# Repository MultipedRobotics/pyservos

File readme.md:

# pyServos

**Still under development**
**Starting to add XL-430 servo**

- pyservos
    - **ServoSerial** - half duplex hardware serial interface using DTR from a USB serial port
    - **PiServoSerial** - half duplex hardware serial interface using a HW pin
    - **utils** - misc
    - **XL320** - register/command/error definitions for Dynamixel's XL-320 servo
    - **AX12** - register/command/error definitions for Dynamixel's AX-12A servo
    - **XL430** - register/command/error definitions for Dynamixel's AX-12A servo

# Setup

## Install

The suggested way to install this is via the `pip` command as follows::

    pip install pyservos

## Development

I am currently using [poetry](https://python-poetry.org/) for my library and using
`pyproject.toml`. To submit git pulls, clone the repository and set it up as
follows:

    git clone https://github.com/MultipedRobotics/pyservos
    cd pyservos
    poetry install
    poety run pytest

# Usage

The `\bin` directory has a number of useful programs to set servo position or ID number. Just
run the command with the `--help` flag to see how to use it.

- `servoAX12`
- `servoXL320` (not implemented)
- `servoXL430` (not implemented)

The above commands have the following format:

 - servoXXX
    - **ping**: find servos on bus, ID[int|**None**]
    - **reboot**: reboot a servo, ID[int|**None**]
    - **reset**: reset a servo, ID[int], level[int]
    - **angle**: set new angle in degrees or radians, angle[float], radians[True|**False**]
    - **baudrate**: set new baudrate, rate[int]
    - **id**: set new ID, current_id[int], new_id[int]
- Values
    - ID: 1-254
    - reset level: 1 (all), 2(all but ID), 3 (all but ID and baudrate)
    - angle: 0-300 degrees
    - rate: 1000000 is default
    - None: if you leave out the value, there is a default that occurs which is safe

# Documentation

- [AX-12A Servo](https://github.com/MomsFriendlyRobotCompany/pyservos/tree/master/docs/ax12)
- [XL-320 Servo](https://github.com/MomsFriendlyRobotCompany/pyservos/tree/master/docs/xl320)
- [XL-430 Servo](https://github.com/MomsFriendlyRobotCompany/pyservos/tree/master/docs/xl430)

A simple example to turn the servo and turn the LED on using a USB serial converter:

```python
# Run an AX-12 servo
from pyservos.servo_serial import ServoSerial
from pyservos.ax12 import AX12

serial = ServoSerial('/dev/tty.usbserial')  # tell it what port you want to use
# serial = ServoSerial('dummy')  # use a dummy serial interface for testing
serial.open()

ax = AX12()
pkt = ax.makeServoPacket(1, 158.6)  # move servo 1 to 158.6 degrees
ret = serial.sendPkt(pkt)  # send packet, I don't do anything with the returned status packet

pkt = ax.makeLEDPacket(1, AX12.LED_ON)
ret = serial.sendPkt(pkt)
```

Although I have made some packet creators (like LED and Servo), you can make
your own using the basic `makeWritePacket` and `makeReadPacket`.

```python
# Run an XL-320 servo
from pyservos.xl320 import XL320
from pyservos.utils import angle2int

xl = XL320()

# let's make our own servo packet that sends servo 3 to 220.1 degrees
ID = 3
reg = XL320.GOAL_POSITION
params = angle2int(220.1)  # convert 220.1 degrees to an int between 0-1023
pkt = xl.makeWritePacket(ID, reg, params)
```

## Dynaixel Servos

## Robot Examples

Here are some example [robots](https://github.com/MultipedRobotics/pyservos/tree/master/docs/robots)

# Other Software

I haven't used these, but they seem good:

- c++: [libdynamixel](https://github.com/resibots/libdynamixel)

# Change Log

| | | |
|------------|-------|--------------------------------------------|
| 2020-01-25 | 2.0.0 | re-architected around protocols rather than servos types |
| 2018-04-30 | 1.0.1 |  API fixes and starting to add 430 support |
| 2018-02-17 | 1.0.0 |  added AX-12 support and renamed the library |
| 2017-04-01 | 0.9.0 |  added python3 support |
| 2017-03-26 | 0.8.0 |  major overhaul and removed the GPIO stuff |
| 2017-03-19 | 0.7.7 |  can switch between GPIO pin and pyserial.setRTS() |
| 2017-02-20 | 0.7.6 |  small fixes and added servo_reboot |
| 2017-01-16 | 0.7.5 |  fixes some small errors |
| 2016-11-29 | 0.7.4 |  add bulk write and small changes |
| 2016-10-11 | 0.7.1 |  small changes/updates |
| 2016-09-12 | 0.7.0 |  refactoring, still working on API |
| 2016-09-05 | 0.5.0 |  published to PyPi |
| 2016-08-16 | 0.0.1 |  init |

# The MIT License (MIT)

Copyright (c) 2016 Kevin J. Walchko

Permission is hereby granted, free of charge, to any person obtaining a copy of
this software and associated documentation files (the "Software"), to deal in
the Software without restriction, including without limitation the rights to
use, copy, modify, merge, publish, distribute, sublicense, and/or sell copies
of the Software, and to permit persons to whom the Software is furnished to do
so, subject to the following conditions:

The above copyright notice and this permission notice shall be included in all
copies or substantial portions of the Software.

THE SOFTWARE IS PROVIDED "AS IS", WITHOUT WARRANTY OF ANY KIND, EXPRESS OR
IMPLIED, INCLUDING BUT NOT LIMITED TO THE WARRANTIES OF MERCHANTABILITY, FITNESS
FOR A PARTICULAR PURPOSE AND NONINFRINGEMENT. IN NO EVENT SHALL THE AUTHORS OR
COPYRIGHT HOLDERS BE LIABLE FOR ANY CLAIM, DAMAGES OR OTHER LIABILITY, WHETHER
IN AN ACTION OF CONTRACT, TORT OR OTHERWISE, ARISING FROM, OUT OF OR IN
CONNECTION WITH THE SOFTWARE OR THE USE OR OTHER DEALINGS IN THE SOFTWARE.

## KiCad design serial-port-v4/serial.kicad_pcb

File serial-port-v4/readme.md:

# Serial Port

## Robotis Suggestion

There are many ways (chip combinations) to achieve this interface.

## My Board

The serial interface talks to both AX-12 (12V power) and XL-320 (8V power)
servos. The design uses SMD parts, but they are all hand solderable.

- RPi TX is attached to a 74LV126 single gate, OE operates when **HIGH**
- RPi RX is attached to a 74LV125 single gate, OE operates when **LOW**
- RPi DTR (any pin really) is connected to the OE on both chips
- Gates are both 5V tolerant on input and have a VCC range of 1.65 - 5.5V
- Both gates are setup for 3.3V operations, with a MOSFET setup to level shift
the DATA line
- The behavior follows the above Robotis suggestion for half duplex operation

[schematic](serial.pdf)

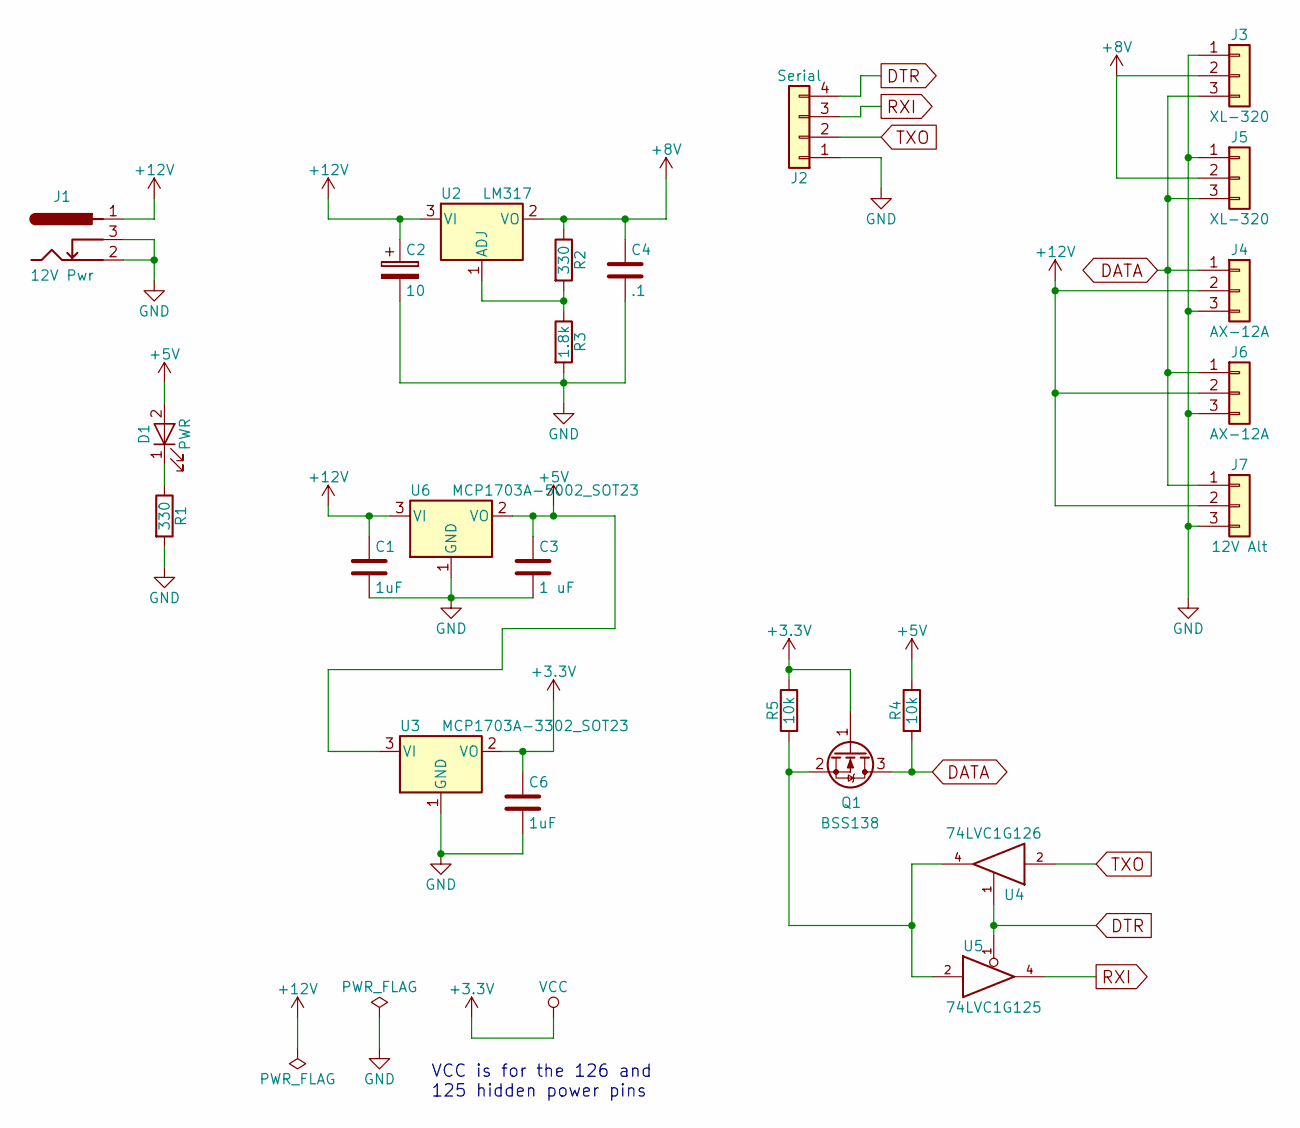
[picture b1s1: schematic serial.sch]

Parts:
C1, C6: 1uF; C_1206_HandSoldering
C2: 10; CP_Radial_D6.3mm_P2.50mm
C3: 1 uF; C_1206_HandSoldering
C4: .1; C_1206_HandSoldering
D1: PWR; LED_1206_HandSoldering
J1: 12V Pwr; BARREL_JACK
J2: Serial; Pin_Header_Straight_1x04_Pitch2.54mm
J3, J5: XL-320; Molex_MicroLatch-53253-0370_03x2.00mm_Straight
J4, J6: AX-12A; Molex_SPOX-5267_22-03-5035_03x2.54mm_Straight
J7: 12V Alt; Pin_Header_Straight_1x03_Pitch2.54mm
Q1: BSS138; SOT-23_Handsoldering
R1, R2: 330; R_1206_HandSoldering
R3: 1.8k; R_1206_HandSoldering
R4, R5: 10k; R_1206_HandSoldering
U2: LM317; TO-220-3_Horizontal
U3: MCP1703A-3302_SOT23; SOT-23_Handsoldering
U4: 74LVC1G126; SOT-23-5_HandSoldering
U5: 74LVC1G125; SOT-23-5_HandSoldering
U6: MCP1703A-5002_SOT23; SOT-23_Handsoldering

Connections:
+3V3: C6.1, Q1.1 (G), R5.1, U3.2 (VO), U4.5 (VCC), U5.5 (VCC)
+5V: C3.1, D1.2 (A), R4.1, U3.3 (VI), U6.2 (VO)
+8V: C4.1, J3.2, J5.2, R2.1, U2.2 (VO)
+12V: C1.1, C2.1, J1.1, J4.2, J6.2, J7.2, U2.3 (VI), U6.3 (VI)
DATA: J3.3, J4.1, J5.3, J6.1, J7.1, Q1.3 (D), R4.2
DTR: J2.4, U4.1, U5.1
GND: C1.2, C2.2, C3.2, C4.2, C6.2, J1.2, J1.3, J2.1, J3.1, J4.3, J5.1, J6.3, J7.3, R1.2, R3.2, U3.1 (GND), U4.3 (GND), U5.3 (GND), U6.1 (GND)
unnamed: D1.1 (K), R1.1
unnamed: Q1.2 (S), R5.2, U4.4, U5.2
unnamed: R2.2, R3.1, U2.1 (ADJ)
RXI: J2.3, U5.4
TXO: J2.2, U4.2

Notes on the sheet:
VCC is for the 126 and 125 hidden power pins

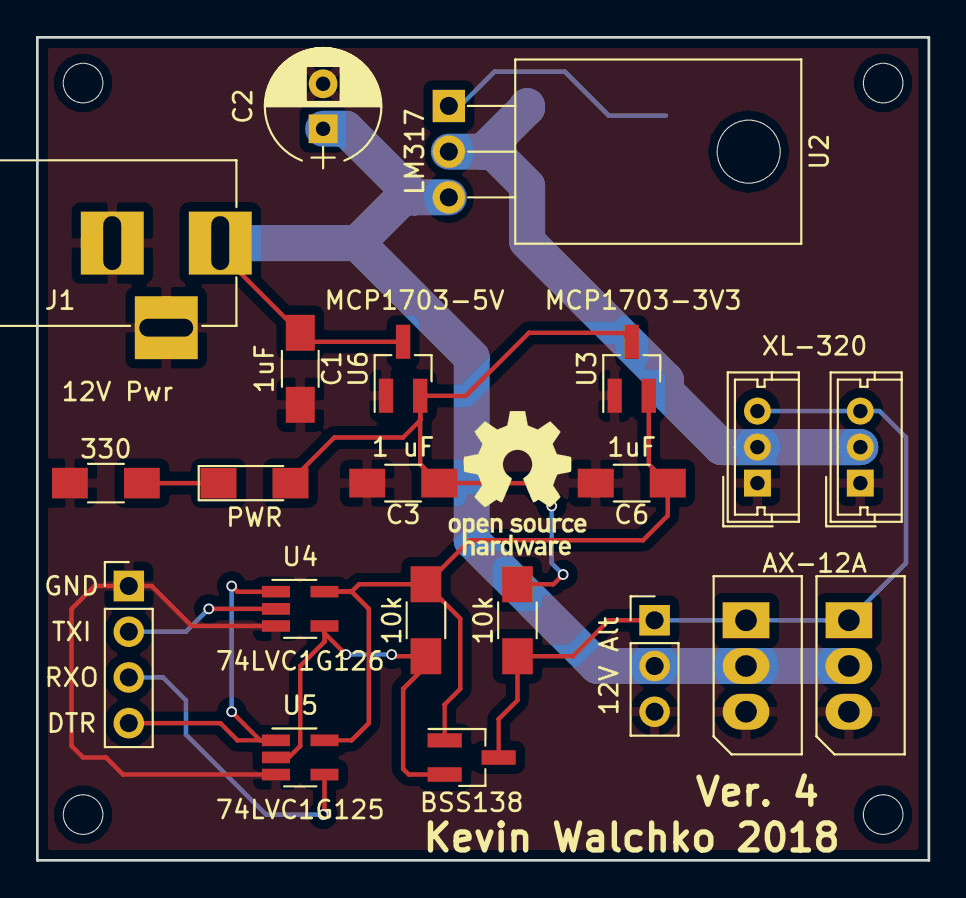
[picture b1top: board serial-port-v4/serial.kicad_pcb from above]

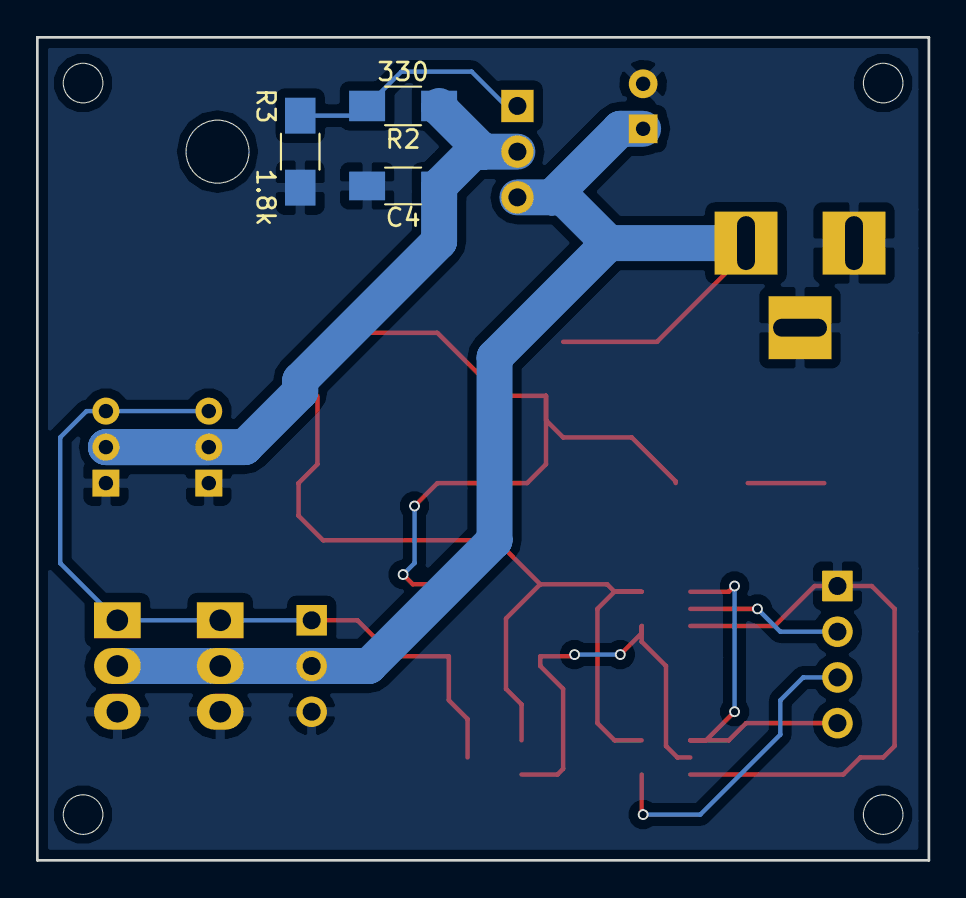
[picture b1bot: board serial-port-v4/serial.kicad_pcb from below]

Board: 2 copper layers, 49.5 x 45.7 mm, 24 parts (3 on the bottom side), 12 nets.

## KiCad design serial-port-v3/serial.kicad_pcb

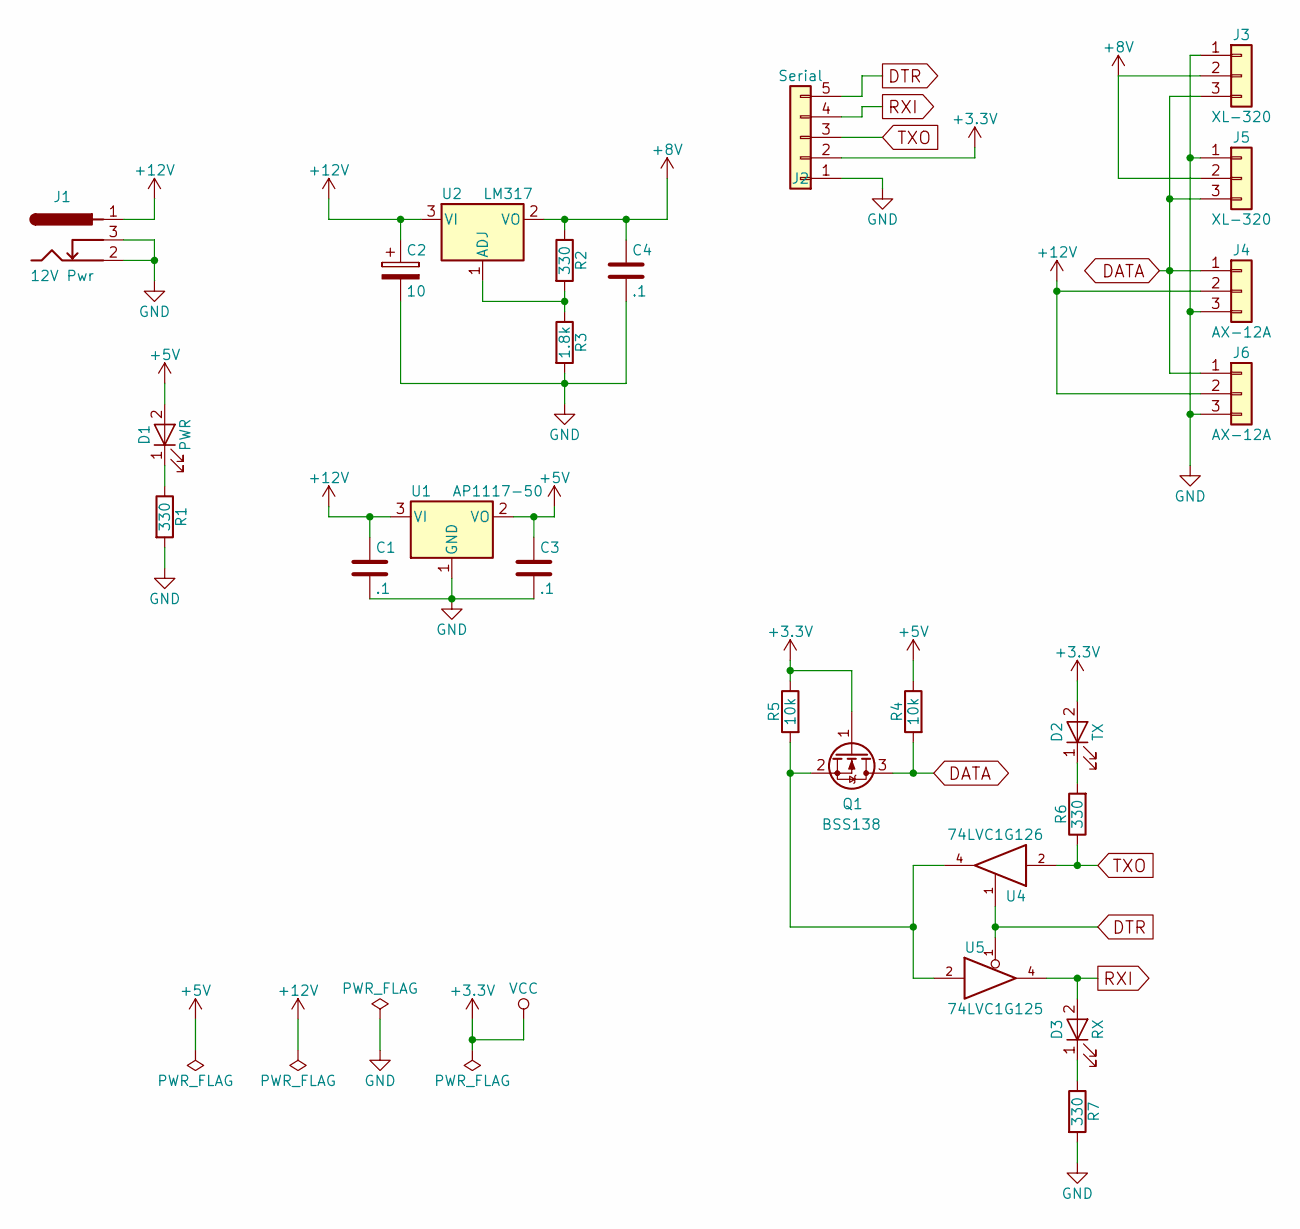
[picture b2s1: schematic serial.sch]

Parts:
C1, C3, C4: .1; C_1206_HandSoldering
C2: 10; CP_Radial_D6.3mm_P2.50mm
D1: PWR; LED_1206_HandSoldering
D2: TX; LED_1206_HandSoldering
D3: RX; LED_1206_HandSoldering
J1: 12V Pwr; BARREL_JACK
J2: Serial; Pin_Header_Straight_1x05_Pitch2.54mm
J3, J5: XL-320; Molex_MicroLatch-53253-0370_03x2.00mm_Straight
J4, J6: AX-12A; Molex_SPOX-5267_22-03-5035_03x2.54mm_Straight
Q1: BSS138; SOT-23
R1, R2, R6, R7: 330; R_1206_HandSoldering
R3: 1.8k; R_1206_HandSoldering
R4, R5: 10k; R_1206_HandSoldering
U1: AP1117-50; SOT-223-3Lead_TabPin2
U2: LM317; TO-220-3_Horizontal
U4: 74LVC1G126; SOT-23-5_HandSoldering
U5: 74LVC1G125; SOT-23-5_HandSoldering

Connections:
+3V3: D2.2 (A), J2.2, Q1.1 (G), R5.1, U4.5 (VCC), U5.5 (VCC)
+5V: C3.1, D1.2 (A), R4.1, U1.2 (VO)
+8V: C4.1, J3.2, J5.2, R2.1, U2.2 (VO)
+12V: C1.1, C2.1, J1.1, J4.2, J6.2, U1.3 (VI), U2.3 (VI)
DATA: J3.3, J4.1, J5.3, J6.1, Q1.3 (D), R4.2
DTR: J2.5, U4.1, U5.1
GND: C1.2, C2.2, C3.2, C4.2, J1.2, J1.3, J2.1, J3.1, J4.3, J5.1, J6.3, R1.2, R3.2, R7.2, U1.1 (GND), U4.3 (GND), U5.3 (GND)
unnamed: D1.1 (K), R1.1
unnamed: D2.1 (K), R6.2
unnamed: D3.1 (K), R7.1
unnamed: Q1.2 (S), R5.2, U4.4, U5.2
unnamed: R2.2, R3.1, U2.1 (ADJ)
RXI: D3.2 (A), J2.4, U5.4
TXO: J2.3, R6.1, U4.2

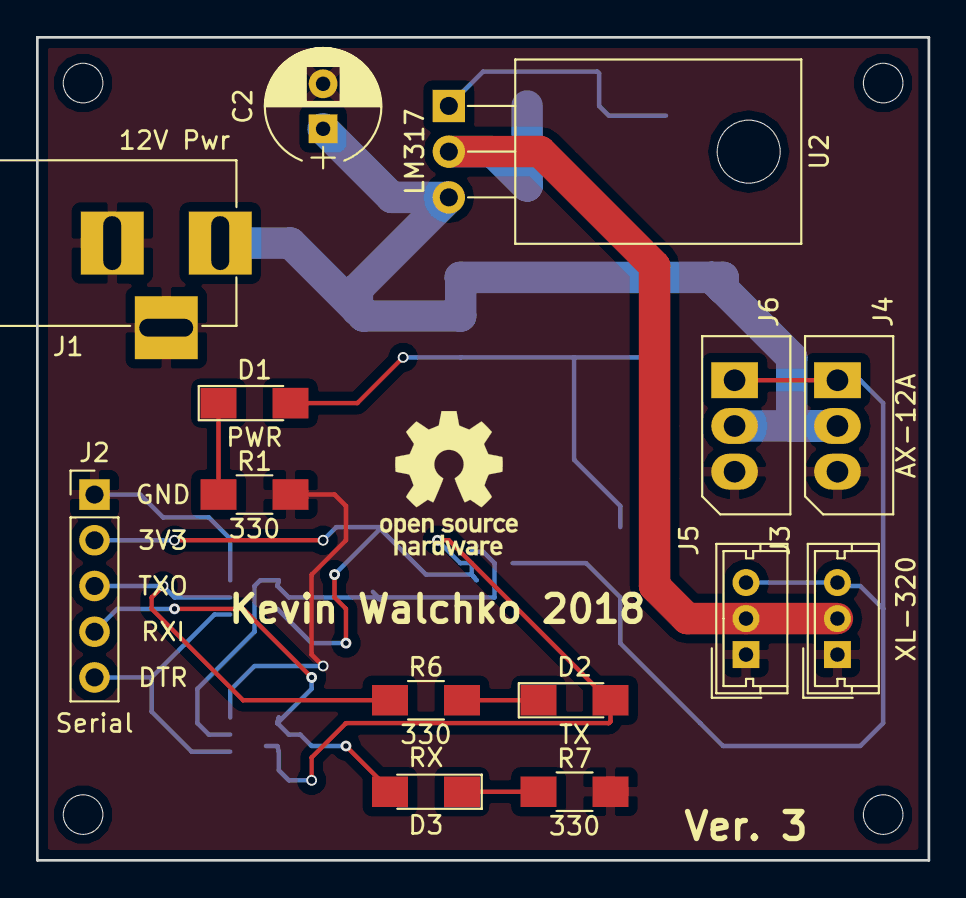
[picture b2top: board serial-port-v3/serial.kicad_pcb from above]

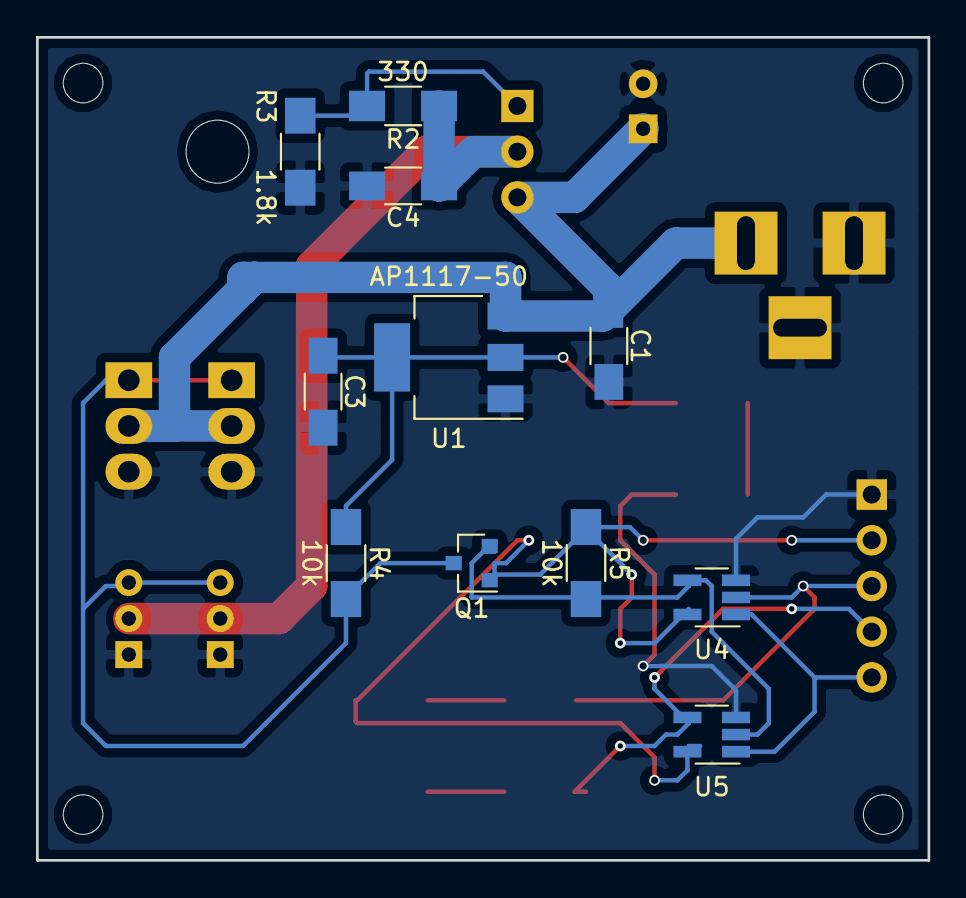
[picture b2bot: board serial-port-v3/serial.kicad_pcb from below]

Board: 2 copper layers, 49.5 x 45.7 mm, 25 parts (11 on the bottom side), 14 nets.

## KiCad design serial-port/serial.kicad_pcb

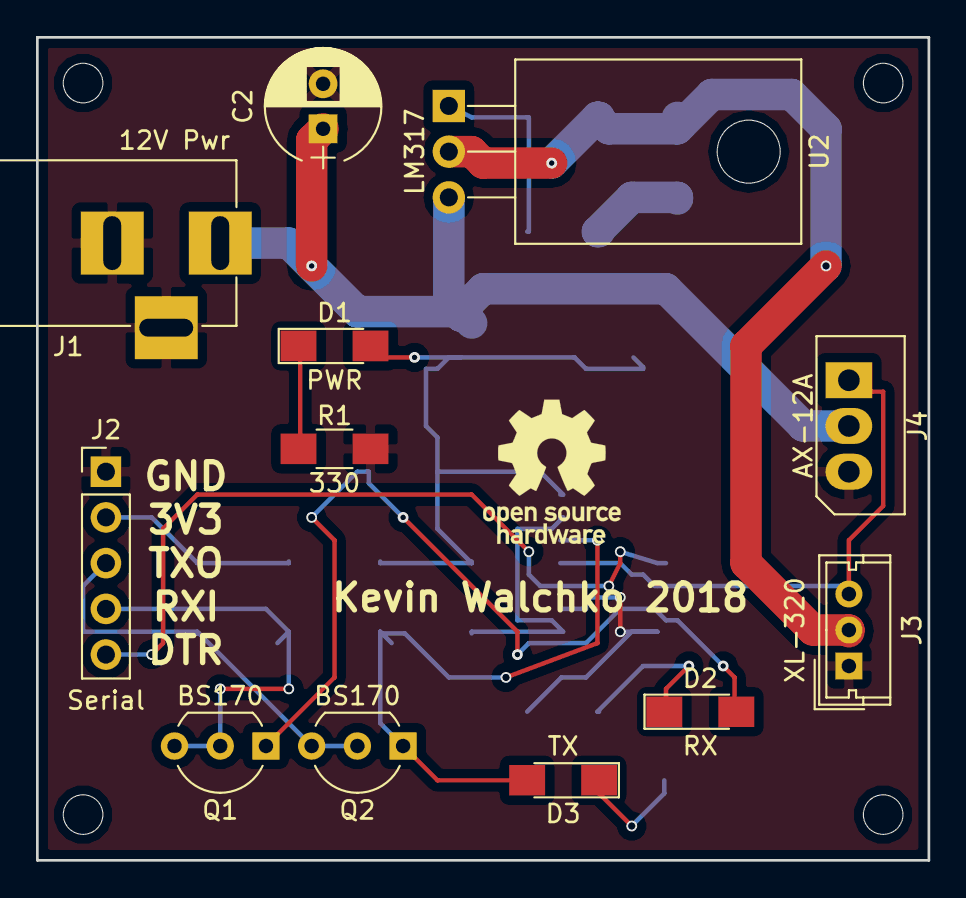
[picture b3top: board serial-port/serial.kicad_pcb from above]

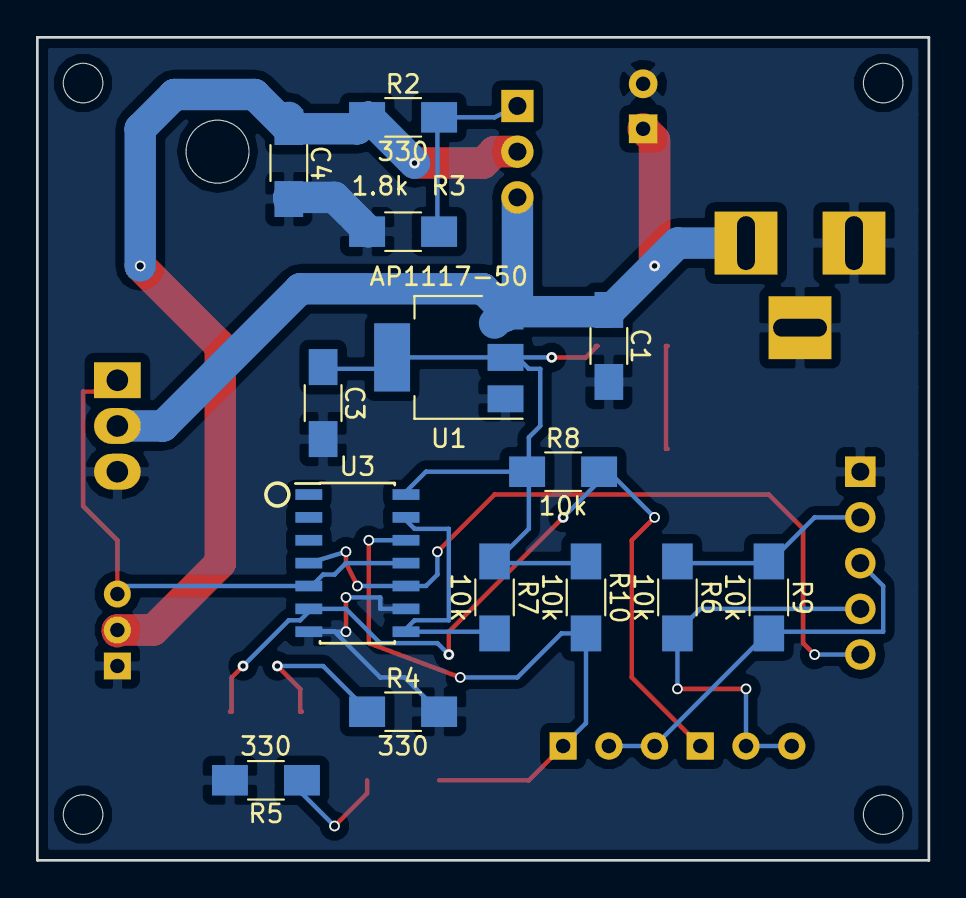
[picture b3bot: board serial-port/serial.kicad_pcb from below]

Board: 2 copper layers, 49.5 x 45.7 mm, 26 parts (14 on the bottom side), 16 nets.

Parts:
C1, C3, C4: .1; C_1206_HandSoldering
C2: 10; CP_Radial_D6.3mm_P2.50mm
D1: PWR; LED_1206_HandSoldering
D2: RX; LED_1206_HandSoldering
D3: TX; LED_1206_HandSoldering
J1: 12V Pwr; BARREL_JACK
J2: Serial; Pin_Header_Straight_1x05_Pitch2.54mm
J3: XL-320; Molex_MicroLatch-53253-0370_03x2.00mm_Straight
J4: AX-12A; Molex_SPOX-5267_22-03-5035_03x2.54mm_Straight
Q1, Q2: BS170; TO-92_Inline_Wide
R1, R2, R4, R5: 330; R_1206_HandSoldering
R3: 1.8k; R_1206_HandSoldering
R6, R7, R8, R9, R10: 10k; R_1206_HandSoldering
U1: AP1117-50; SOT-223-3_TabPin2
U2: LM317; TO-220-3_Horizontal
U3: 74LS126; SOIC-14_3.9x8.7mm_Pitch1.27mm

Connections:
+3V3: J2.2, R6.1, R9.1
+5V: C3.1, D1.2, R7.1, R8.1, R10.1, U1.2, U3.14
+8V: C4.1, J3.2, R2.1, U2.2
+12V: C1.1, C2.1, J1.1, J4.2, U1.3, U2.3
DATA: J3.3, J4.1, U3.5, U3.11
DTR: J2.5, U3.4, U3.10
GND: C1.2, C2.2, C3.2, C4.2, J1.2, J1.3, J2.1, J3.1, J4.3, R1.2, R3.2, R4.2, R5.2, U1.1, U3.7, U3.9
unnamed: D1.1, R1.1
unnamed: D2.1, R4.1
unnamed: D3.1, R5.1
unnamed: R2.2, R3.1, U2.1
unnamed: R7.2, U3.8, U3.13
RXI: D2.2, Q1.1, R8.2, U3.6
RXI3v3: J2.4, Q1.2, Q1.3, R6.2
TXO: D3.2, Q2.1, R10.2, U3.12
TXO3v3: J2.3, Q2.2, Q2.3, R9.2

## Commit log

2018-02-17 init
2018-02-17 link fixes
2018-02-17 reorg
2018-02-18 docs update
2018-02-18 doc cleanup
2018-02-18 320 working?
2018-03-03 added serial port board
2018-03-04 serial port fixes
2018-03-06 psb update
2018-03-06 board fixes
2018-03-17 mosfet fix?
2018-04-19 architecting new api to include more servos
2018-04-27 Create deleteme
2018-05-26 pi working
2018-05-26 ping updaate
2018-06-10 serial version 4 done
2018-06-19 added pdf
2018-11-24 clean up
2020-01-07 update ... working new interface
2020-01-25 fix :bento:
2020-01-25 up :bento:
2021-03-21 Fix of makeSyncMoveSpeedPacket (tested) and makeSyncMovePacket (untested).
